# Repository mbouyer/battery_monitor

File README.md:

# battery_monitor
12V battery monitoring

This project includes 2 boards for a service 12V Pb battery monitoring.

The main board monitors the battery voltage and current, using a microchip PAC1953 chip and a precision shunt resistor. It uses a pic18f with integrated CAN controller, and connects to a CAN bus network. Along with instant voltage and current values, the pic18f will be able to compute and report the battery SoC. As the PAC1953 has 3 channels, it will also be able to monitor other sources, like solar panel or the engine battery. The main battery will be monitored with an external, high current shunt resistor (100A/50mV) so one of the on-board shunt resitor won't be soldered.

The second board will convert the voltage across the high current shunt resistor to a voltage (between 0.5 and 4.5V) suitable to drive a pannel-mounted Osculati  +/-50A ampmeter(27.320.23). As I don't expect to have currents more than 20A here, I computed the gain so that the indicator range is +/-25A (that is, the indicated value will be twice the real value). Two potentiometers allows to adjust the 0 and the gain. This, along with an external analog voltmeter, provides a second, independant battery monitoring tool.

car battery, engine and solar panel icons by [Icons8](https://icons8.com)

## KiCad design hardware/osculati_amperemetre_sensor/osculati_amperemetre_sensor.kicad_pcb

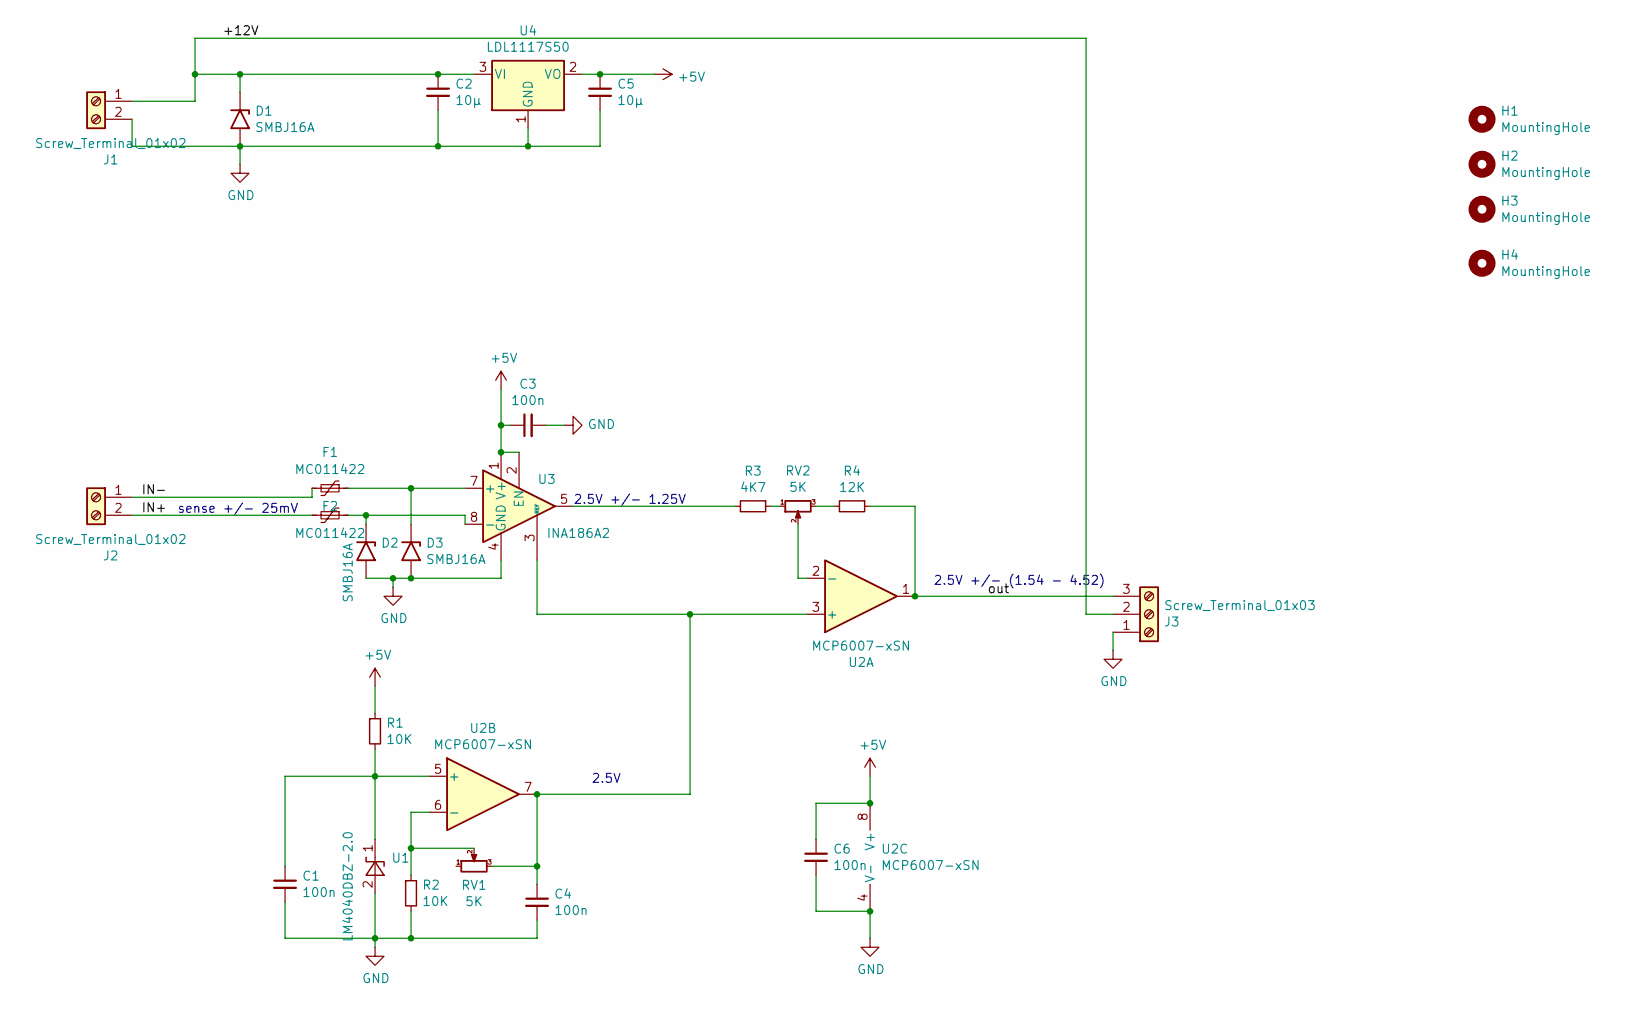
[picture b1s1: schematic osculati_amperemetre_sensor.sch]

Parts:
C1, C3, C4, C6: 100n; C_0805_2012Metric_Pad1.18x1.45mm_HandSolder
C2: 10µ; C_1210_3225Metric_Pad1.33x2.70mm_HandSolder
C5: 10µ; C_0805_2012Metric_Pad1.18x1.45mm_HandSolder
D1, D2, D3: SMBJ16A; D_SMB
F1, F2: MC011422; R_0603_1608Metric_Pad0.98x0.95mm_HandSolder
H1, H2, H3, H4: MountingHole; MountingHole_3.2mm_M3_DIN965
J1, J2: Screw_Terminal_01x02; MC24356
J3: Screw_Terminal_01x03; TerminalBlock_bornier-3_P5.08mm
R1, R2: 10K; R_1206_3216Metric_Pad1.30x1.75mm_HandSolder
R3: 4K7; R_0805_2012Metric_Pad1.20x1.40mm_HandSolder
R4: 12K; R_0805_2012Metric_Pad1.20x1.40mm_HandSolder
RV1, RV2: 5K; T93XA
U1: LM4040DBZ-2.0; SOT-23
U2: MCP6007-xSN; SOIC-8_3.9x4.9mm_P1.27mm
U3: INA186A2; SOT-23-8_Handsoldering
U4: LDL1117S50; SOT-223-3_TabPin2

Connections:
+5V: C3.1, C5.1, C6.1, R1.1, U2.8 (V+), U3.1 (V+), U3.2 (EN), U4.2 (VO)
/+12V: C2.1, D1.1 (A1), J1.1, J3.2, U4.3 (VI)
/IN+: F2.2, J2.2
/IN-: F1.2, J2.1
/out: J3.3, R4.1, U2.1
GND: C1.2, C2.2, C3.2, C4.2, C5.2, C6.2, D1.2 (A2), D2.2 (A2), D3.2 (A2), J1.2, J3.1, R2.2, U1.2 (A), U2.4 (V-), U3.4 (GND), U4.1 (GND)
unnamed: C1.1, R1.2, U1.1 (K), U2.5 (+)
unnamed: C4.1, RV1.3, U2.3 (+), U2.7, U3.3 (REF)
unnamed: D2.1 (A1), F2.1, U3.8 (-)
unnamed: D3.1 (A1), F1.1, U3.7 (+)
unnamed: R2.1, RV1.2, U2.6 (-)
unnamed: R3.1, RV2.1
unnamed: R3.2, U3.5
unnamed: R4.2, RV2.3
unnamed: RV2.2, U2.2 (-)

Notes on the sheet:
sense +/- 25mV
2.5V
2.5V +/- 1.25V
2.5V +/- (1.54 - 4.52)

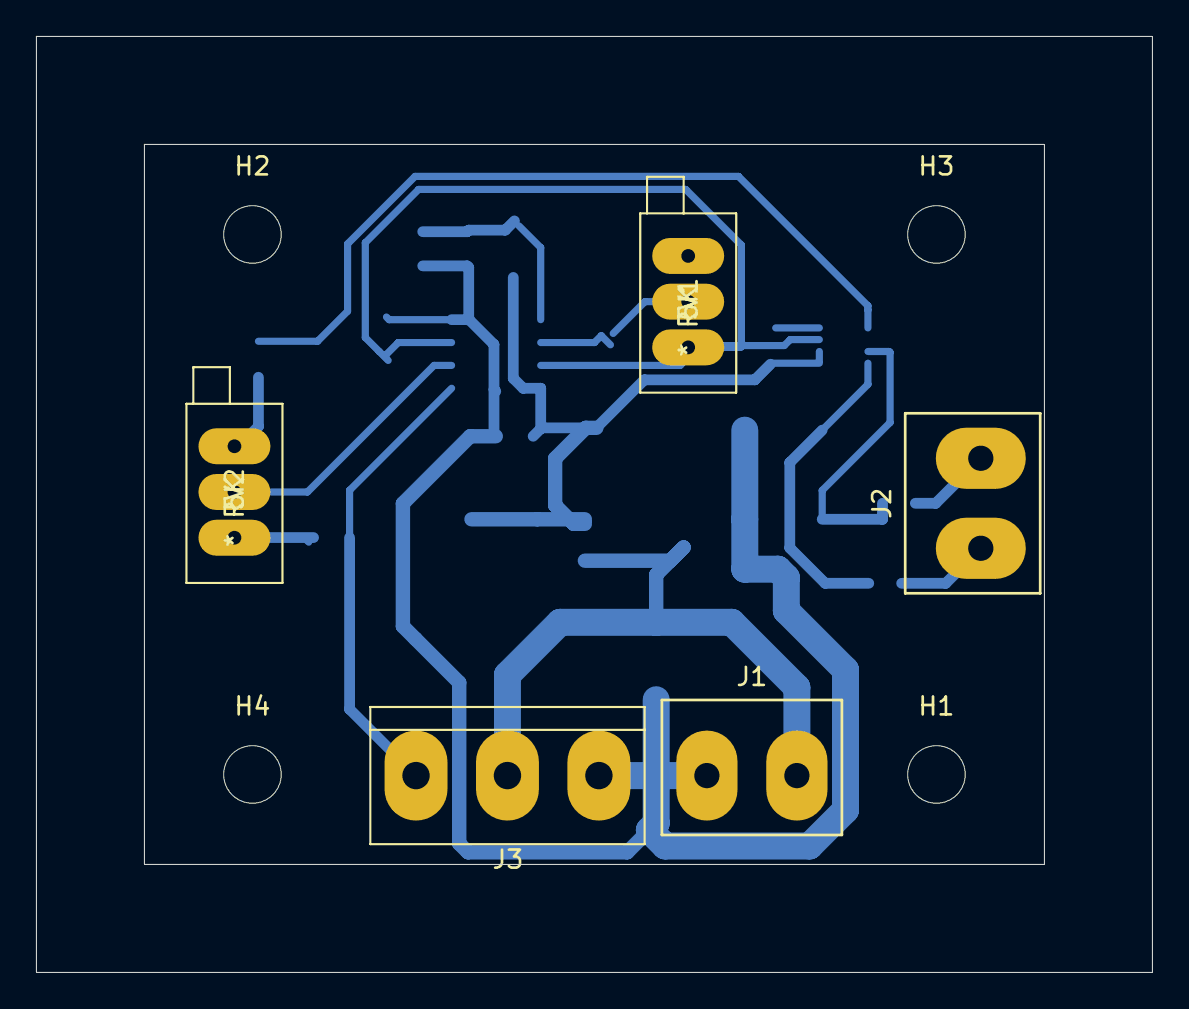
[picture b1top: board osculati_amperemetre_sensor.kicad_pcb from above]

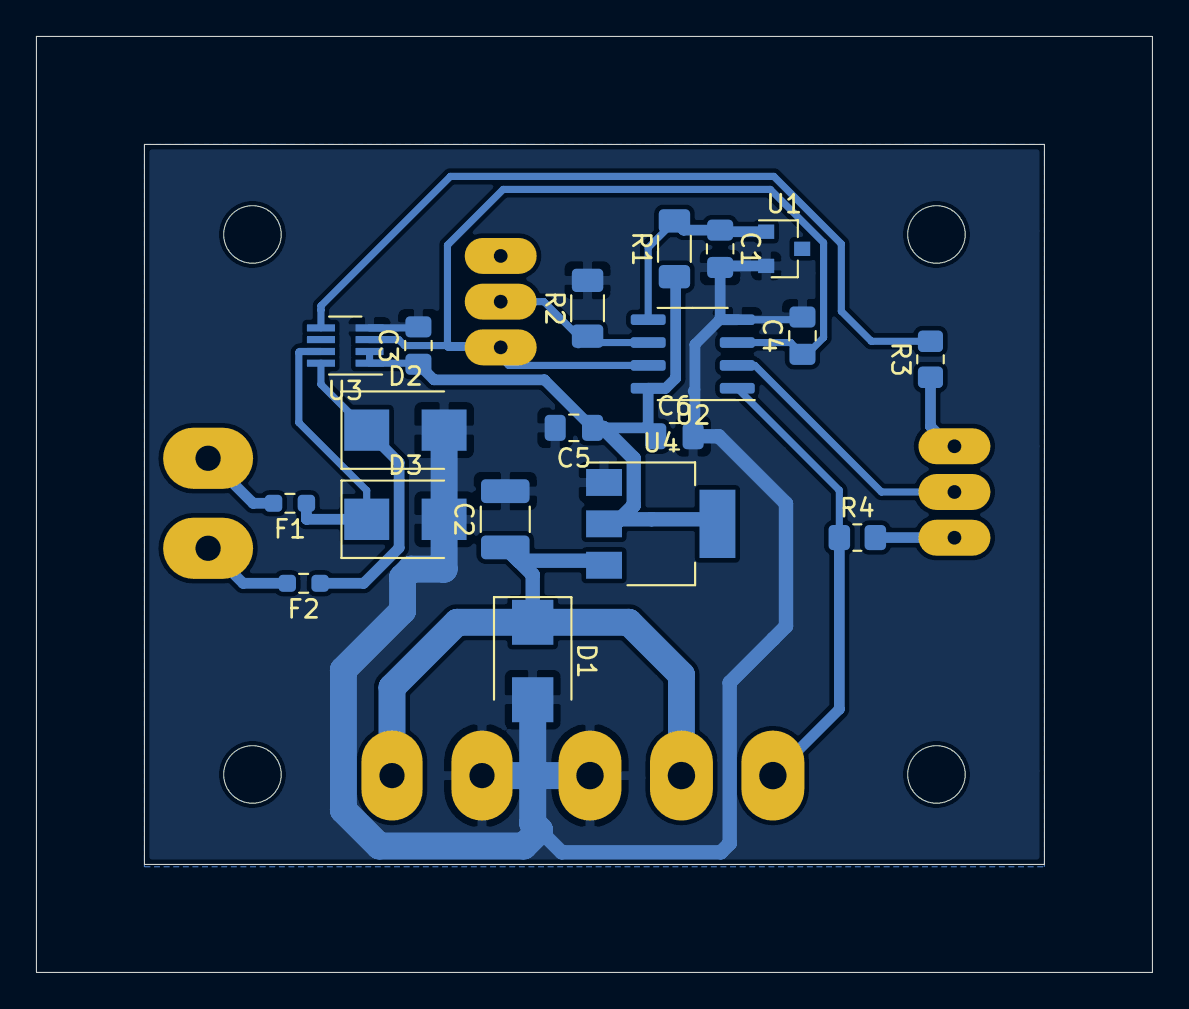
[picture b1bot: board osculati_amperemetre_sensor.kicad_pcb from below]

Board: 2 copper layers, 62.0 x 52.0 mm, 28 parts (19 on the bottom side), 15 nets.

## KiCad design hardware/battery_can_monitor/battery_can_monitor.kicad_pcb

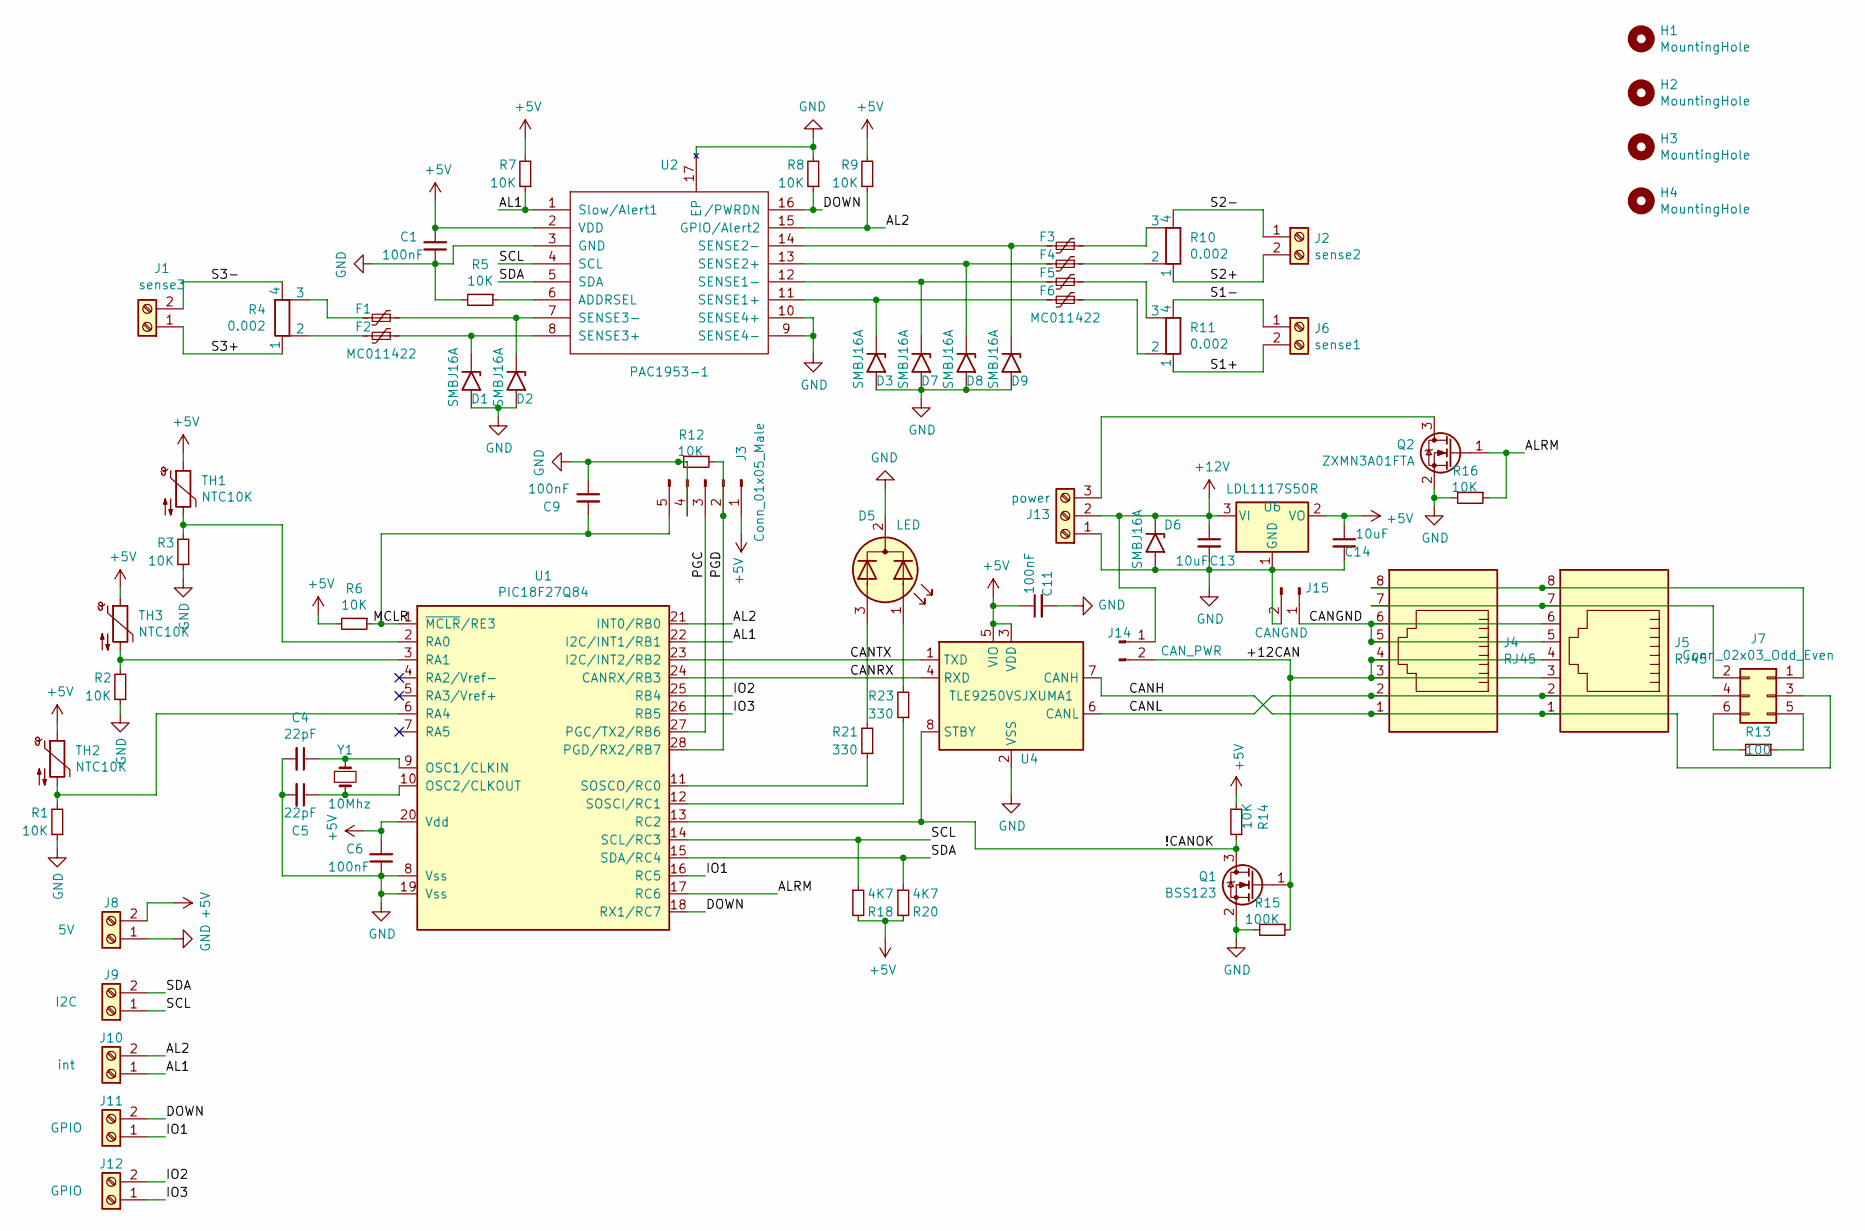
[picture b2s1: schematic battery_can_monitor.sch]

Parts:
C1, C6, C9, C11: 100nF; C_0805_2012Metric_Pad1.18x1.45mm_HandSolder
C4, C5: 22pF; C_Disc_D3.8mm_W2.6mm_P2.50mm
C13: 10uF; C_1210_3225Metric_Pad1.33x2.70mm_HandSolder
C14: 10uF; C_0805_2012Metric_Pad1.18x1.45mm_HandSolder
D1, D2, D3, D6, D7, D8, D9: SMBJ16A; D_SMB_Handsoldering
D5: LED; LED_D3.0mm-3
F1, F2, F3, F4, F5, F6: MC011422; R_0603_1608Metric_Pad0.98x0.95mm_HandSolder
H1, H2, H3, H4: MountingHole; MountingHole_3.2mm_M3_DIN965
J1: sense3; TerminalBlock_MetzConnect_Type703_RT10N02HGLU_1x02_P9.52mm_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
J2: sense2; TerminalBlock_MetzConnect_Type703_RT10N02HGLU_1x02_P9.52mm_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
J3: Conn_01x05_Male; PinHeader_1x05_P2.54mm_Vertical
J4, J5: RJ45; RJ45_Amphenol_54602-x08_Horizontal
J6: sense1; TerminalBlock_MetzConnect_Type703_RT10N02HGLU_1x02_P9.52mm_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
J7: Conn_02x03_Odd_Even; PinHeader_2x03_P2.54mm_Vertical
J8: 5V; TerminalBlock_TE_282834-2_1x02_P2.54mm_Horizontal
J9: I2C; TerminalBlock_TE_282834-2_1x02_P2.54mm_Horizontal
J10: int; TerminalBlock_TE_282834-2_1x02_P2.54mm_Horizontal
J11, J12: GPIO; TerminalBlock_TE_282834-2_1x02_P2.54mm_Horizontal
J13: power; TerminalBlock_bornier-3_P5.08mm
J14: CAN_PWR; PinHeader_1x02_P2.54mm_Vertical
J15: CANGND; PinHeader_1x02_P2.54mm_Vertical
Q1: BSS123; SOT-23
Q2: ZXMN3A01FTA; SOT-23
R1, R2, R3, R8, R12: 10K; R_1206_3216Metric_Pad1.30x1.75mm_HandSolder
R4, R10, R11: 0.002; R-Shunt_2512_6332Metric_Pad1.40x3.35mm_HandSolder
R5, R6, R7, R9, R14, R16: 10K; R_Axial_DIN0207_L6.3mm_D2.5mm_P7.62mm_Horizontal
R13: 100; R_0805_2012Metric_Pad1.20x1.40mm_HandSolder
R15: 100K; R_Axial_DIN0207_L6.3mm_D2.5mm_P7.62mm_Horizontal
R18, R20: 4K7; R_Axial_DIN0207_L6.3mm_D2.5mm_P7.62mm_Horizontal
R21, R23: 330; R_Axial_DIN0207_L6.3mm_D2.5mm_P7.62mm_Horizontal
TH1, TH2, TH3: NTC10K; TerminalBlock_TE_282834-2_1x02_P2.54mm_Horizontal
U1: PIC18F27Q84; SOIC-28W_7.5x17.9mm_P1.27mm
U2: PAC1953-1; VQFN-16-1EP_3x3mm_P0.5mm_EP1.1x1.1mm
U4: TLE9250VSJXUMA1; SOIC-8_3.9x4.9mm_P1.27mm
U6: LDL1117S50R; SOT-223-3_TabPin2
Y1: 10Mhz; Crystal_HC18-U_Vertical

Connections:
+5V: C1.2, C6.2, C11.1, C14.1, J3.1, J8.2, R6.2, R7.2, R9.2, R14.2, R18.2, R20.2, TH1.1, TH2.1, TH3.1, U1.20 (Vdd), U2.2 (VDD), U4.3 (VDD), U4.5 (VIO), U6.2 (VO)
+12V: C13.1, D6.1 (A1), J13.2, J14.1, U6.3 (VI)
/!CANOK: Q1.3 (D), R14.1, U1.13 (RC2), U4.8 (STBY)
/+12CAN: J4.3, J4.4, J5.3, J5.4, J14.2, Q1.1 (G), R15.1
/AL1: J10.1, R7.1, U1.22 (I2C/INT1/RB1), U2.1 (Slow/Alert1)
/AL2: J10.2, R9.1, U1.21 (INT0/RB0), U2.15 (GPIO/Alert2)
/ALRM: Q2.1 (G), R16.1, U1.17 (RC6)
/CANGND: J4.5, J4.6, J5.5, J5.6, J15.1
/CANH: J4.1, J5.1, J7.3, U4.7 (CANH)
/CANL: J4.2, J5.2, J7.4, U4.6 (CANL)
/CANRX: U1.24 (CANRX/RB3), U4.4 (RXD)
/CANTX: U1.23 (I2C/INT2/RB2), U4.1 (TXD)
/DOWN: J11.2, R8.1, U1.18 (RX1/RC7), U2.16 (/PWRDN)
/IO1: J11.1, U1.16 (RC5)
/IO2: J12.2, U1.25 (RB4)
/IO3: J12.1, U1.26 (RB5)
/MCLR: C9.2, J3.5, R6.1, U1.1 (~MCLR~/RE3)
/PGC: J3.3, U1.27 (PGC/TX2/RB6)
/PGD: J3.2, R12.1, U1.28 (PGD/RX2/RB7)
/S1+: J6.2, R11.1
/S1-: J6.1, R11.4
/S2+: J2.2, R10.1
/S2-: J2.1, R10.4
/S3+: J1.1, R4.1
/S3-: J1.2, R4.4
/SCL: J9.1, R18.1, U1.14 (SCL/RC3), U2.4 (SCL)
/SDA: J9.2, R20.1, U1.15 (SDA/RC4), U2.5 (SDA)
GND: C1.1, C4.2, C5.2, C6.1, C9.1, C11.2, C13.2, C14.2, D1.2 (A2), D2.2 (A2), D3.2 (A2), D5.2 (K), D6.2 (A2), D7.2 (A2), D8.2 (A2), D9.2 (A2), J3.4, J8.1, J13.1, J15.2, Q1.2 (S), Q2.2 (S), R1.1, R2.1, R3.1, R5.2, R8.2, R12.2, R15.2, R16.2, U1.8 (Vss), U1.19 (Vss), U2.3 (GND), U2.9 (SENSE4-), U2.10 (SENSE4+), U2.17 (EP), U4.2 (VSS), U4.9 (VSS), U6.1 (GND)
unnamed: C4.1, U1.9 (OSC1/CLKIN), Y1.1
unnamed: C5.1, U1.10 (OSC2/CLKOUT), Y1.2
unnamed: D1.1 (A1), F2.1, U2.8 (SENSE3+)
unnamed: D2.1 (A1), F1.1, U2.7 (SENSE3-)
unnamed: D3.1 (A1), F6.2, U2.11 (SENSE1+)
unnamed: D5.1 (A1), R23.2
unnamed: D5.3 (A2), R21.2
unnamed: D7.1 (A1), F5.2, U2.12 (SENSE1-)
unnamed: D8.1 (A1), F4.2, U2.13 (SENSE2+)
unnamed: D9.1 (A1), F3.2, U2.14 (SENSE2-)
unnamed: F1.2, R4.3
unnamed: F2.2, R4.2
unnamed: F3.1, R10.3
unnamed: F4.1, R10.2
unnamed: F5.1, R11.3
unnamed: F6.1, R11.2
unnamed: J4.7, J5.7, J7.2
unnamed: J4.8, J5.8, J7.1
unnamed: J7.5, R13.1
unnamed: J7.6, R13.2
unnamed: J13.3, Q2.3 (D)
unnamed: R1.2, TH2.2, U1.6 (RA4)
unnamed: R2.2, TH3.2, U1.3 (RA1)
unnamed: R3.2, TH1.2, U1.2 (RA0)
unnamed: R5.1, U2.6 (ADDRSEL)
unnamed: R21.1, U1.11 (SOSCO/RC0)
unnamed: R23.1, U1.12 (SOSCI/RC1)

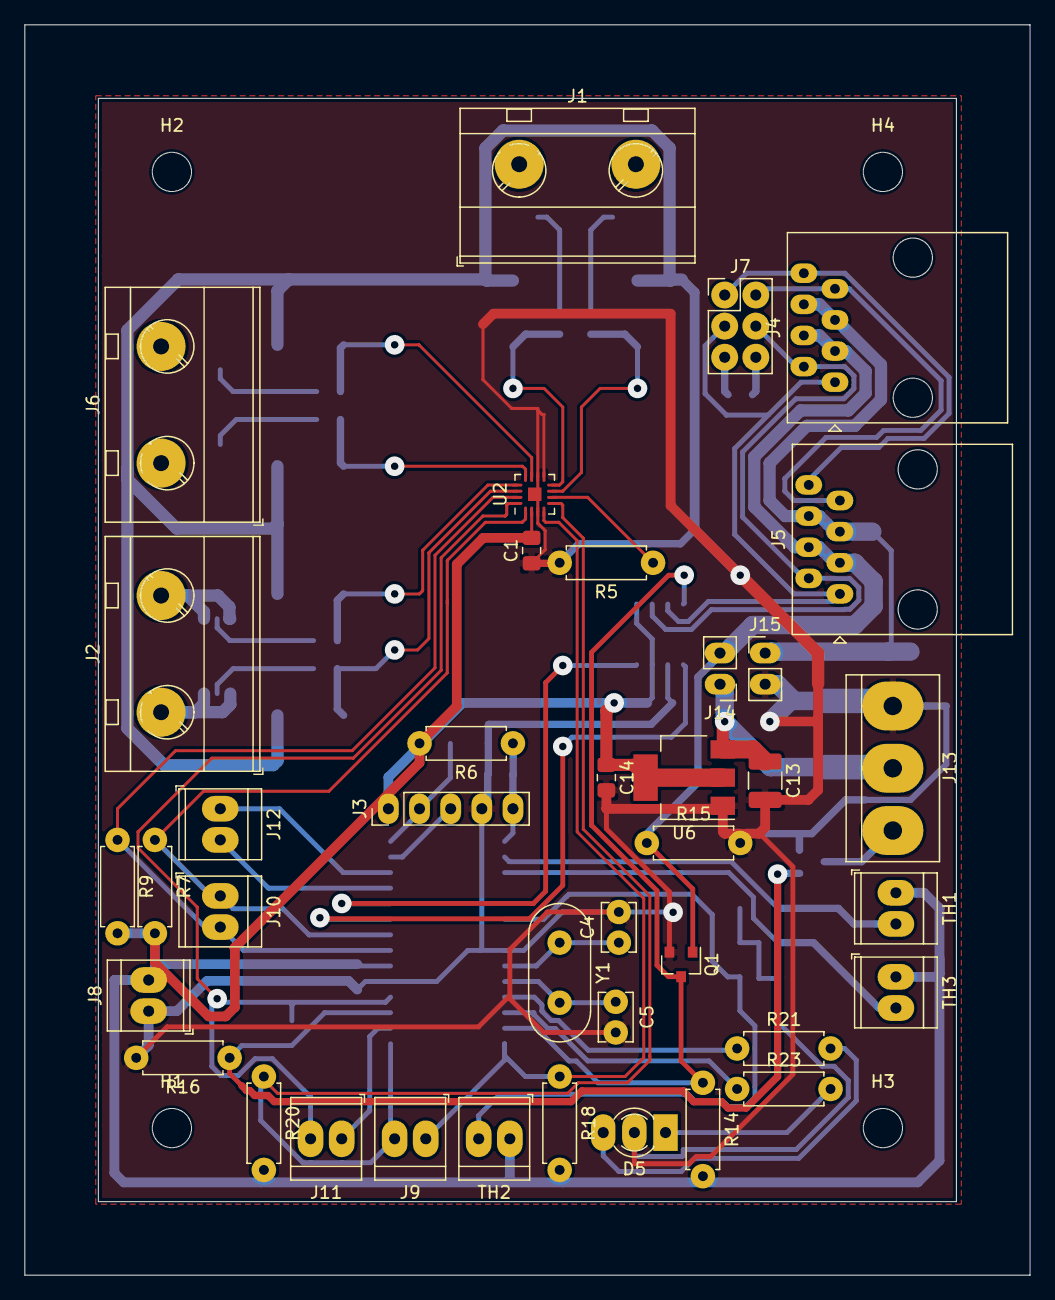
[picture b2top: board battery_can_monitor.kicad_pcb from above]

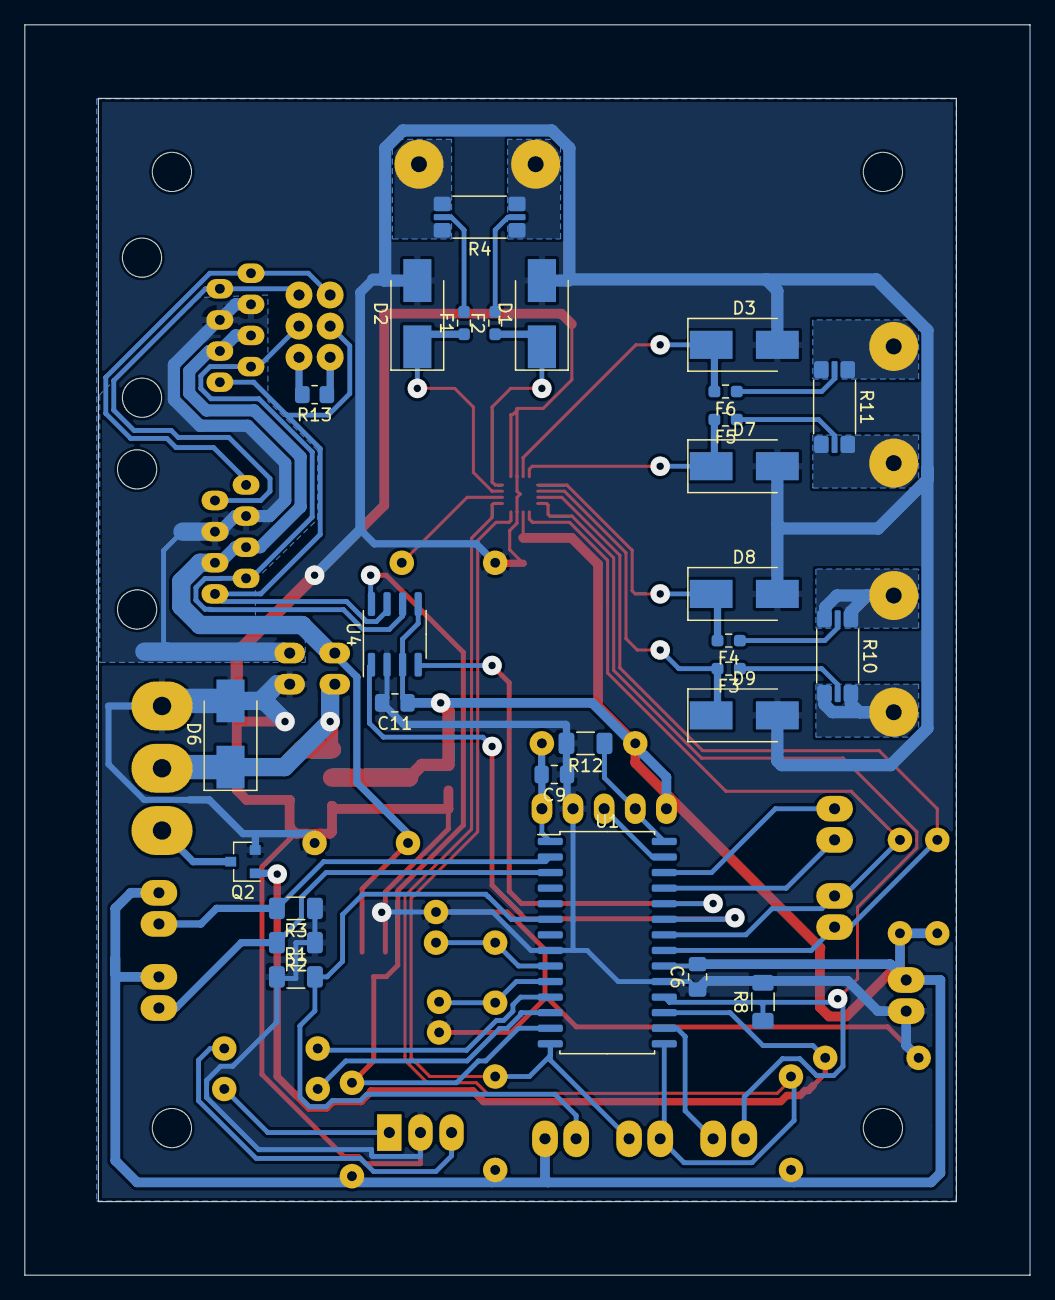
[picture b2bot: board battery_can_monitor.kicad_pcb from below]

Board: 2 copper layers, 82.0 x 102.0 mm, 71 parts (28 on the bottom side), 55 nets.

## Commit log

2021-12-12 Initial commit of hardware kicad files, ready for first rev production
2021-12-13 Restore proper hole size for RJ45 connectors.
2021-12-13 Keep coating on the front side for through-hole connectors pads (we can't solder them anyway)
2021-12-13 Add fab outputs for mask and paste
2021-12-13 Add mask/paste fabrication files
2021-12-20 Add a 6mm margin around PCB.
2021-12-20 Regen fabrication outputs.
2022-01-28 Fix name of connectors (sense1/sense2 swapped)
2022-02-01 Test version of the canbus battery monitor software. Lots of functions missing but good enough to test main functionalities (pic18, pac1953, CAN)
2022-02-06 Less verbose on retry
2022-02-06 Read voltage on all channels every 1/10s. Read accum, and compute average voltage and current for all channels every seconds.
2022-02-06 Use the disable bit from ctrl register to skip channels.
2022-02-07 Reorganise reading values from the pac195x. Send battery_status one per second, one instance every 10ms.
2022-02-13 Update fabrication files.
2022-02-13 Properly use the NCANOK signal to manage the can bus.
2022-02-13 swap green & red LEDs to match hardware.
2022-02-16 Add mounting holes dimentions
2022-02-16 Tie floating pins to GND. Get temperatures from thermistors.
2022-02-18 Add drawings for the box holding the PCBs
2022-03-06 Correct results with calibration data.
2022-04-03 Add a log (in flash) to keep track of battery voltage/current/temperature.
2022-04-05 WIP on a battery status app
2022-04-05 Make timeout erase display
2022-04-09 Work in progress on log retrieval
2022-04-10 Fix invalid temp in log
2022-04-10 Make sure to add 0x100 to idx on the last log packet of a page
2022-04-10 Fix temperature in log packet
2022-04-10 On packet boundary don't send a log entry twice.
2022-04-10 Implement generation number, incremented on each log rollover
2022-04-10 WIP: request and print log from BM.
2022-04-10 data is Amps * 100, not * 1000
2022-04-10 Make sure to not count duplicate frames
2022-04-10 More complete log retrieval management, with timeout and retransmit.
2022-04-10 2 digits after dot is enough for amps (we don't have better data)
2022-06-22 Add some icons from Icons8, and use the car battery as the app icon
2022-06-22 Credit Icons8
2022-06-22 constify
2022-06-22 Support custom text labels or icons from the config file
2022-07-03 If the temperature is very low, assume there's no sensor
2022-07-03 If we need to resend a command, also reset the current index
2022-07-03 work in progress on log: store all log entries in a std::vector; update when new entries are available
2022-07-03 Work in progress on log: we can now write the log file. Attempt to set timestamp of entries.
2022-07-03 Comment out GTK2 detection, we're mostly using GTK3 now
2022-07-03 Fix log time and write Read log file at startup
2022-07-04 Split log management to a separate file
2022-07-19 Convert labels to wxButtons
2022-07-20 Revert "Convert labels to wxButtons", it was not a good idea
2022-07-20 Parse command line, and implement -L to disable log retrieval
2022-09-06 Add a View menu, with an entry to show the log window Add a dummy text entry to the log window for testing purposes Make the log windows show up
2022-09-07 Build with wxmathplot
2022-09-07 Add wxmathplot as module
2022-09-07 First text with wxmathplot
2022-09-07 bmlogstorage: add support to get current, next of previous block
2022-09-07 Continue wxmathplot experiments: plot all instance intensity
2022-09-07 Amps graph is useable
2022-09-07 Trace all 3 graphs
2022-09-07 Convert temp to degC
2022-09-08 Remember log window size/pos
2022-09-08 log: another debug printf, print the interval between log entries.
2022-09-08 Redefine mpScaleX for something more appropriate for our use case.
2022-09-08 Use localtime for X axis
2022-09-08 bmScaleX: use red for label sticks try to use tick intervals that make sense (multiple of days, hours or 30mn when appropriate)
2022-09-08 Redefine mpInfoCoords to have a more appropriate display
2022-09-08 No need to have x= and y= in bmInfoCoord
2022-09-08 Improve temperature display
2022-09-08 invert current sign in displays, > 0 is charging and < 0 discharging.
2022-09-08 No need to call mathplot's UpdateAll() in OnShow() handler.
2022-09-08 Reimplement events ID with wxID_HIGHEST
2022-09-08 Abuse bmScaleX::Plot() to send an event when scale or position may have changed. Use this to sync the X view on all 3 plots.
2022-09-09 Set icon for the bmlog frame too.
2022-09-09 Factor out config and instance labels in wxbm class.
2022-09-09 wxFlexGridSizer: use NINST, not hardcoded value
2022-09-09 bmlog: add a column to display some informative values
2022-09-09 Factor out layers data setup in its own function; to be used to dynamically change the data set. Read log data from OnShow() instead of setup, so that we'll always show the most up to date data on in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
2022-09-10 Don't try to update non-existent instance
2022-09-10 Display log statistics
2022-09-11 Clear log_entries before re-reading a log block.
2022-09-11 GetBoundingBox() doens't give the coordinates of the actual view; use GetDesiredXmin/GetDesiredXmax() instead
2022-09-11 Make log window prettier.
2022-09-11 bmmathplot: handle small step values; avoids infinite loop
2022-09-11 In addition to Ah, also print average current
2022-09-11 remove debug printf
2022-09-11 Make the intensity statistics aligned
2022-09-11 Add a flag for entries whose time can be trusted
2022-09-12 bmlog: start implemnting a top bar with prev/next buttons, zoom setting and time range information
2022-09-12 Set zoom value with actual time duration
2022-09-12 Rename timezoom to timescale Handle time scale input
2022-09-13 Clean up trailing whitespaces.
2022-09-13 Make the previous/next buttons navigate in the current block
2022-09-13 getLogBlock(): If we're going to copy new entries to the provided vector, clear it. This simplifies end-of-log handling in the caller.
2022-09-13 Implement previous/next accross blocks
2022-09-13 Shut up debug printfs
2022-09-13 Add a Fit button
2022-09-13 SetScaleX/SetPosX() doesn't update GetDesiredXmin/Xmax. So update mp_startX/mp_endX from changed graph
2022-09-14 Don't sleep if we have more work to do (softintrs != 0). Should fix timer drift.
2022-09-15 Rework bmInfoCoords: mark the closest date to the mouse pointer with a vertical line on all graphs, and display all parameters for this date in a top region.
2022-09-15 Remove debug printf Adjust graph margins
2022-09-15 SetTimeMark(): log_entries[].time make not have the values used for the plots, so use the plot vectors instead.
2022-09-16 Allow to toggle graphs, by click on graph label.
2022-09-16 bmInfoCoords doesn't have to be a mpInfoLayer; a mpLayer is enough
2022-09-16 bmInfoCoords: Display a horizontal line and corresponding value on mouse position. Avoid segfault on mouse click on graph.
2022-09-16 We're not getting wxEVT_LEAVE_WINDOW events in bmInfoCoords. Instead check mouseX/Y against the plot dimentions.
    Make sure setTimeMark(-1) will DTRT.
2022-09-17 Don't try to read data from vector if there are none available.
2022-09-17 Always refresh graph if !isnan(m_y). Even if time didn't change, y may have changed.
2022-09-17 If we get a PRIVATE_LOG_REPLY frame with no entry, signal it as PRIVATE_LOG_ERROR_LAST. Avoids repeated timeout when the last entry happens to be at the end of a log block.
2022-09-17 Make sure there's enough space for the date info
2022-09-17 In main window, map tCTRL+L to SHOWLOG
2022-09-17 Close the log window with ctrl-W
2022-09-18 Split out log block complete handling out of addLogEntry, so that it's possible to signal a block complete without adding an entry; as is the case when we get a log packet with no entries. PRIVATE_LO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
2022-09-25 Do not send a log block with 0 entries, instead reply with PRIVATE_LOG_ERROR_NOTFOUND or PRIVATE_LOG_ERROR_LAST as appropriate. This makes the protocol more coherent.
2022-09-25 We're not supposed to get empty log blocks now, so log it if it happens,
2022-11-10 Show the BM address in the N2K dialog
2022-11-14 Fix amps assembly from log messages.

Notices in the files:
parts and their libraries:
Copyright 2021 Accelerated Designs. All rights reserved.
